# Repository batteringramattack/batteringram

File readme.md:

# Battering RAM: Low-Cost Interposer Attacks on Confidential Computing via Dynamic Memory Aliasing

This repository contains the hardware design and firmware for the interposer, tools, and proof-of-concept and end-to-end attacks presented in our paper.

## Directory structure

This repository is organized as follows.

* `./ddr4-interposer` contains the hardware design for the DDR4 interposer.
* `./interposer-control` contains the firmware for the DDR4 interposer.
* `./scalable-sgx-attacks` contains contains the PoC and E2E attacks on Scalable SGX.

## Getting started

### Hardware requirements

This artifact requires a custom DDR4 interposer to introduce dynamic memory aliases. The hardware schematic and PCB files for this interposer can be found in `./ddr4-interposer`. Below is the bill of materials.

| **Component**     | **Cost**  | **Qty.** | **Part number**        |
|-------------------|-------|:----:|---------------------|
| DIMM Connector    | $16   | 1    | CONN-DDR4-288-SM    |
| Raspberry Pi Pico | $5    | 1    | Raspberry Pi Pico 2 |
| Analog Switches   | $4    | 2    | ADG902BRMZ          |
| Voltage regulator | $0.65 | 1    | LD1117S25TR         |
| Resistor, 0402, 1kOhm     | $0.005 | 2    |            |
| Capacitor, 0603, 100nF    | $0.02  | 3    |            |
| Capacitor, 1206, 10uF     | $0.018 | 1    |            |

### Creating aliases

The interposer creates aliases by tying certain row address lines to ground. This causes aliases in the CPU's physical memory space as the DIMM now always sees a low signal, regardless of the address sent out by the CPU.

The interposer has five footprints that can be populated with switches. These footprints are labeled in the silkscreen. These include three footprints for inserting the switches on the A11, A13, and A17 lines (labeled "A11->A11", "A13->A13", and "A17->A17", respectively).
If a switch is not installed in a footprint, a jumper must be soldered in its place to connect the CPU and DIMM lines without interruption.

Additionally, to bypass RCD parity checking, two additional footprints optionally allow the A11 or A13 signals to be redirected to A17 (labeled "A11->A17" and "A13->A17", respectively).
Note that only one of these footprints can be occupied at a time. These switches can also not be used in conjunction with the "A17->A17" switch. When installing a switch on these footprints, you must also connect the corresponding jumper to connect it to the A17 line on the DIMM side.

### Mapping out unstable and aliased regions in Linux

When RCD parity is enabled, unstable memory regions are created where only a single bit is flipped, resulting in a parity error. Additionally, writes to aliased memory regions while the interposer is active may accidentally overwrite critical memory regions, potentially causing the system to crash.
To avoid these issues, the use of both the unstable regions and aliased regions can be prevented by using the `memmap` kernel parameter:
```
memmap=nn$ss
```
This will mark region `ss` to `ss+nn` as reserved. Note that using this parameter in GRUB requires escaping the `$` as `\$`. If you enter it through `/etc/default/grub`, you also have to escape the `\`:
```
GRUB_CMDLINE_LINUX_DEFAULT="memmap=nn\\\$ss"
```

## Cite

```
@inproceedings{batteringramsp26,
  title     = {{Battering RAM}: Low-Cost Interposer Attacks on Confidential Computing via Dynamic Memory Aliasings},
  author    = {De Meulemeester, Jesse and Oswald, David and Verbauwhede, Ingrid and Van Bulck, Jo},
  booktitle = {47th {IEEE} Symposium on Security and Privacy ({S\&P})},
  month     = May,
  year      = 2026,
}
```

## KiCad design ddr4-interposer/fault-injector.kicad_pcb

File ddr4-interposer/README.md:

# Battering RAM interposer

This directory contains the schematics and PCB layout (KiCad) of the Battering RAM interposer.

The interposer is configurable: it has several footprints for analog switches, of which only a few are populated, depending on which address lines you want to manipulate. The sections below describe which parts are always required, which depend on the configuration, and the configurations we used in the paper.

## Bill of materials

| Description               | Reference             | Part number         | Populate          |
|---------------------------|-----------------------|---------------------|-------------------|
| DDR4 DIMM connector       | J2                    | CONN-DDR4-288-SM    | Always            |
| Raspberry Pi Pico 2       | U3                    | Raspberry Pi Pico 2 | Always            |
| Voltage regulator, 2.5 V  | U8                    | LD1117S25TR         | Always            |
| Capacitor, 1206, 10 µF    | C9                    |                     | Always            |
| Capacitor, 0603, 100 nF   | C8                    |                     | Always            |
| Analog switch             | U1, U2, U4–U7, U9     | ADG902BRMZ          | Per configuration |
| Resistor, 0402, 1 kΩ      | R1–R7                 |                     | Per configuration |
| Capacitor, 0603, 100 nF   | C1–C7                 |                     | Per configuration |
| Jumper, 0402, 0 Ω         | R8, R9, R11, R13, R17 |                     | Per configuration |

## Switch positions

The interposer has seven switch positions:

- **In-line switches** (U4, U1, U6) sit in the path of the A11, A13 and A17 command/address (CA) lines. They are labeled `Axx -> Axx` on the silkscreen.
- **Redirect switches** (U5, U2) connect the CPU-side A11 or A13 line to the DIMM-side A17 line. They are labeled `Axx -> A17` on the silkscreen. To connect the switch output to the DIMM, the output jumper must be populated.
- **General-purpose switches** (U7, U9) are not connected to any signal. They can be wired to any signal by cutting the bridged jumpers and connecting them to the test points using using thin enameled (magnet) wire.

Each switch has its own pull-up resistor and decoupling capacitor. Each in-line switch also has a passthrough jumper that connects the line directly when the switch is not populated.

| Switch  | CPU-side line | DIMM-side line | Passthrough jumper | Pull-up | Decoupling cap | Output Jumper |
|:-------:|:-------------:|:--------------:|:------------------:|:-------:|:--------------:|:-------------:|
| U4      | A11           | A11            | R11                | R4      | C2             | -             |
| U1      | A13           | A13            | R13                | R1      | C3             | -             |
| U6      | A17           | A17            | R17                | R5      | C5             | -             |
| U5      | A11           | A17            | –                  | R3      | C4             | R8            |
| U2      | A13           | A17            | –                  | R2      | C1             | R9            |
| U7      | TP2 / TP11    | TP6 / TP12     | –                  | R6      | C6             | -             |
| U9      | TP8 / TP9     | TP7 / TP10     | –                  | R7      | C7             | -             |

## Configuring the interposer
 
Each populated switch needs a pull-up resistor (1 kΩ) and a 100 nF decoupling capacitor, see the table above. In-line switches (U4, U1, U6) that are left unpopulated need their passthrough jumper instead, otherwise the corresponding address line is not connected to the DIMM. The exception is A17 when one of the redirect switches (U5, U2) is installed: the redirect switch then drives A17, so R17 is left unpopulated.
 
> [!NOTE]
> Each DIMM-side line must be driven by exactly one path: its in-line switch, its passthrough jumper, or (for A17) one of the redirect switches. For example, populating both U5 (A11 -> A17) and U6 (A17 -> A17), or U2 (A13 -> A17) together with R17, is invalid, as both would drive A17 on the DIMM.

### Bridged jumpers on other signals

Besides the switch positions, many other signals pass through 0402 jumper footprints (JP1–JP20 and JP23–JP43) that are bridged on the PCB by default. This includes most of the CA bus (all address lines except A11, A13 and A17, which go through the switch positions), the clock, reset and chip-select lines, among others. These signals work as-is without populating anything.

To manipulate one of these signals, cut the bridge between the jumper pads to interrupt the line, and wire the two pads to one of the general-purpose switches (U7, U9). To restore the original connection later, simply solder a 0402 0 Ω resistor onto the footprint.

## Configurations used in the paper

### Single switch (Figure 5a)

| Populate                               | Passthrough jumpers |
|----------------------------------------|---------------------|
| U1 (A13 -> A13) with R1, C3            | R11, R17            |

### Redirecting an address line (Figure 5b)

| Populate                               | Passthrough jumpers |
|----------------------------------------|---------------------|
| U1 (A13 -> A13) with R1, C3            | R11                 |
| U2 (A13 -> A17) with R2, C1, R9        |                     |

### Dual switches (Figure 5c)

| Populate                               | Passthrough jumpers |
|----------------------------------------|---------------------|
| U4 (A11 -> A11) with R4, C2            | R17                 |
| U1 (A13 -> A13) with R1, C3            |                     |

## Fabrication

Recommended settings when ordering the PCB:

- Layers: 4
- PCB thickness: 1.6 mm (or 1.4 mm if available, see note below)
- Min via: 0.2 mm drill / 0.35 mm diameter
- Surface finish: ENIG
- Copper weight: 1 oz outer / 0.5 oz inner
- Everything else: fab default settings (no controlled impedance or special stack-up required)

> [!NOTE]
> 1.6 mm is slightly thicker than regular DDR4 memory modules (1.4 mm). To avoid damaging the motherboard's DIMM socket, it is recommended to use a DDR4 DIMM extender between the motherboard and the interposer.

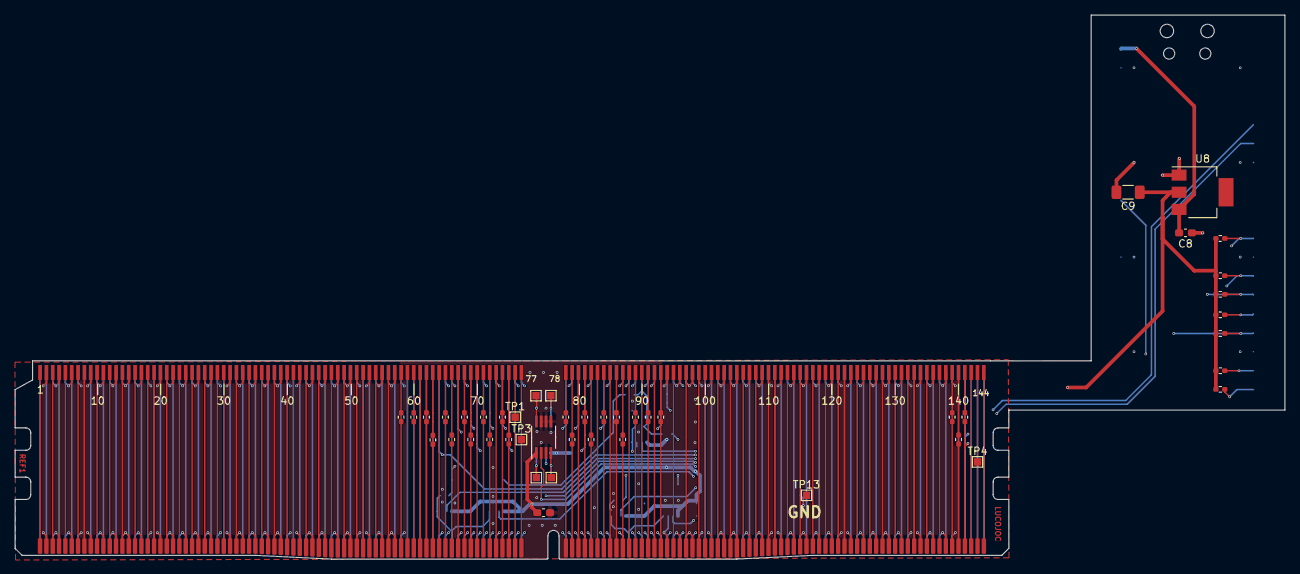
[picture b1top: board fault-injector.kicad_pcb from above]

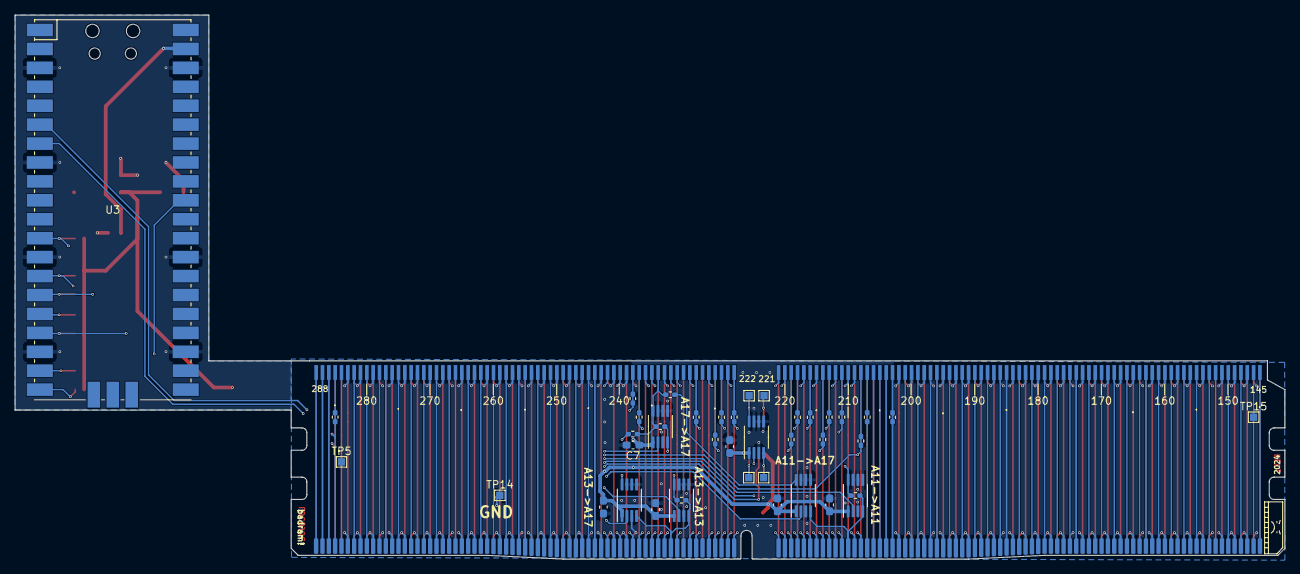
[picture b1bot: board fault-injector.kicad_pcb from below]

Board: 4 copper layers, 170.4 x 73.0 mm, 88 parts (41 on the bottom side), 219 nets.

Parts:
C1, C2, C3, C4, C5, C6, C7: C_Small; C_0603_1608Metric_Pad1.08x0.95mm_HandSolder
C8: 100nF; C_0603_1608Metric_Pad1.08x0.95mm_HandSolder
C9: 10uF; C_1206_3216Metric_Pad1.33x1.80mm_HandSolder
J1: DDR4_to_MB; ddr4-edge-conn-male
J2: DDR4_to_DIMM; ddr4-edge-conn-female-badram
JP1, JP2, JP3, JP4, JP5, JP6, JP7, JP8, JP9, JP10, JP11, JP12, JP13, JP14, JP15, JP16, JP17, JP18, JP19, JP20, JP23, JP24, JP25, JP26, JP27, JP28, JP29, JP30, JP31, JP32, JP33, JP34, JP35, JP36, JP37, JP38, JP39, JP40, JP41, JP42, JP43: Jumper_2_Bridged; Jumper_0402_bridged
R1, R2, R3, R4, R5, R6, R7: 1k; R_0402_1005Metric_Pad0.72x0.64mm_HandSolder
R8, R9: 0; R_0402_1005Metric_Pad0.72x0.64mm_HandSolder
R11, R13, R17: 0R; R_0402_1005Metric_Pad0.72x0.64mm_HandSolder
TP1, TP2, TP3, TP4, TP5, TP6, TP7, TP8, TP9, TP10, TP11, TP12, TP13, TP14, TP15: TestPoint; TestPoint_Pad_1.0x1.0mm
U1, U2, U4, U5, U6, U7, U9: ADG902BRMZ; MSOP-8_3x3mm_P0.65mm
U3: Pico; RPi_Pico_SMD_TH
U8: LD1117S25TR_SOT223; SOT-223-3_TabPin2

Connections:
A0_DIMM: J2.79 (A0), JP43.2 (B)
A0_MB: J1.79 (A0), JP43.1 (A)
A1_DIMM: J2.72 (A1), JP42.2 (B)
A1_MB: J1.72 (A1), JP42.1 (A)
A2_DIMM: J2.216 (A2), JP41.2 (B)
A2_MB: J1.216 (A2), JP41.1 (A)
A3_DIMM: J2.71 (A3), JP40.2 (B)
A3_MB: J1.71 (A3), JP40.1 (A)
A4_DIMM: J2.214 (A4), JP39.2 (B)
A4_MB: J1.214 (A4), JP39.1 (A)
A5_DIMM: J2.213 (A5), JP38.2 (B)
A5_MB: J1.213 (A5), JP38.1 (A)
A6_DIMM: J2.69 (A6), JP37.2 (B)
A6_MB: J1.69 (A6), JP37.1 (A)
A7_DIMM: J2.211 (A7), JP36.2 (B)
A7_MB: J1.211 (A7), JP36.1 (A)
A8_DIMM: J2.68 (A8), JP35.2 (B)
A8_MB: J1.68 (A8), JP35.1 (A)
A9_DIMM: J2.66 (A9), JP34.2 (B)
A9_MB: J1.66 (A9), JP34.1 (A)
A10_AP_DIMM: J2.225 (A10/AP), JP33.2 (B)
A10_AP_MB: J1.225 (A10/AP), JP33.1 (A)
A11_DIMM: J2.210 (A11), R11.2, U4.8 (RF2)
A11_MB: J1.210 (A11), R11.1, U4.4 (RF1), U5.4 (RF1)
A12_BC_n_DIMM: J2.65 (A12/BC_n), JP32.2 (B)
A12_BC_n_MB: J1.65 (A12/BC_n), JP32.1 (A)
A13_DIMM: J2.232 (A13), R13.2, U1.8 (RF2)
A13_MB: J1.232 (A13), R13.1, U1.4 (RF1), U2.4 (RF1)
A17_DIMM: J2.234 (A17), R8.1, R9.1, R17.2, U6.8 (RF2)
A17_MB: J1.234 (A17), R17.1, U6.4 (RF1)
ACT_n_DIMM: J2.62 (ACT_n), JP12.2 (B)
ACT_n_MB: J1.62 (ACT_n), JP12.1 (A)
ALERT_n_DIMM: J2.208 (ALERT_n), JP20.2 (B)
ALERT_n_MB: J1.208 (ALERT_n), JP20.1 (A), U3.31 (GPIO26_ADC0)
BA0_DIMM: J2.81 (BA0), JP28.2 (B)
BA0_MB: J1.81 (BA0), JP28.1 (A)
BA1_DIMM: J2.224 (BA1), JP27.2 (B)
BA1_MB: J1.224 (BA1), JP27.1 (A)
BG0_DIMM: J2.63 (BG0), JP9.2 (B)
BG0_MB: J1.63 (BG0), JP9.1 (A)
BG1_DIMM: J2.207 (BG1), JP8.2 (B)
BG1_MB: J1.207 (BG1), JP8.1 (A)
CAS_n_A15_DIMM: J2.86 (CAS_n/A15), JP30.2 (B)
CAS_n_A15_MB: J1.86 (CAS_n/A15), JP30.1 (A)
CB0_DIMM: J1.49 (CB0), J2.49 (CB0)
CB1_DIMM: J1.194 (CB1), J2.194 (CB1)
CB2_DIMM: J1.56 (CB2), J2.56 (CB2)
CB3_DIMM: J1.201 (CB3), J2.201 (CB3)
CB4_DIMM: J1.47 (CB4), J2.47 (CB4)
CB5_DIMM: J1.192 (CB5), J2.192 (CB5)
CB6_DIMM: J1.54 (CB6), J2.54 (CB6)
CB7_DIMM: J1.199 (CB7), J2.199 (CB7)
CK0_c_DIMM: J2.75 (CK0_c), JP6.2 (B)
CK0_c_MB: J1.75 (CK0_c), JP6.1 (A)
CK0_t_DIMM: J2.74 (CK0_t), JP5.2 (B)
CK0_t_MB: J1.74 (CK0_t), JP5.1 (A)
CK1_c_DIMM: J2.219 (CK1_c), JP3.2 (B)
CK1_c_MB: J1.219 (CK1_c), JP3.1 (A)
CK1_t_DIMM: J2.218 (CK1_t), JP2.2 (B)
CK1_t_MB: J1.218 (CK1_t), JP2.1 (A)
CKE0_DIMM: J2.60 (CKE0), JP7.2 (B)
CKE0_MB: J1.60 (CKE0), JP7.1 (A)
CKE1_NC_DIMM: J2.203 (CKE1/NC), JP4.2 (B)
CKE1_NC_MB: J1.203 (CKE1/NC), JP4.1 (A)
CS0_n_DIMM: J2.84 (CS0_n), JP26.2 (B)
CS0_n_MB: J1.84 (CS0_n), JP26.1 (A)
CS1_n_NC_DIMM: J2.89 (CS1_n/NC), JP25.2 (B)
CS1_n_NC_MB: J1.89 (CS1_n/NC), JP25.1 (A)
CS2_n_C0_DIMM: J2.93 (CS2_n/C0), JP24.2 (B)
CS2_n_C0_MB: J1.93 (CS2_n/C0), JP24.1 (A)
CS3_n_C1,NC_DIMM: J2.237 (CS3_n/C1,NC), JP23.2 (B)
CS3_n_C1,NC_MB: J1.237 (CS3_n/C1,NC), JP23.1 (A)
DQ0_DIMM: J1.5 (DQ0), J2.5 (DQ0)
DQ1_DIMM: J1.150 (DQ1), J2.150 (DQ1)
DQ2_DIMM: J1.12 (DQ2), J2.12 (DQ2)
DQ3_DIMM: J1.157 (DQ3), J2.157 (DQ3)
DQ4_DIMM: J1.3 (DQ4), J2.3 (DQ4)
DQ5_DIMM: J1.148 (DQ5), J2.148 (DQ5)
DQ6_DIMM: J1.10 (DQ6), J2.10 (DQ6)
DQ7_DIMM: J1.155 (DQ7), J2.155 (DQ7)
DQ8_DIMM: J1.16 (DQ8), J2.16 (DQ8)
DQ9_DIMM: J1.161 (DQ9), J2.161 (DQ9)
DQ10_DIMM: J1.23 (DQ10), J2.23 (DQ10)
DQ11_DIMM: J1.168 (DQ11), J2.168 (DQ11)
DQ12_DIMM: J1.14 (DQ12), J2.14 (DQ12)
DQ13_DIMM: J1.159 (DQ13), J2.159 (DQ13)
DQ14_DIMM: J1.21 (DQ14), J2.21 (DQ14)
DQ15_DIMM: J1.166 (DQ15), J2.166 (DQ15)
DQ16_DIMM: J1.27 (DQ16), J2.27 (DQ16)
DQ17_DIMM: J1.172 (DQ17), J2.172 (DQ17)
DQ18_DIMM: J1.34 (DQ18), J2.34 (DQ18)
DQ19_DIMM: J1.179 (DQ19), J2.179 (DQ19)
DQ20_DIMM: J1.25 (DQ20), J2.25 (DQ20)
DQ21_DIMM: J1.170 (DQ21), J2.170 (DQ21)
DQ22_DIMM: J1.32 (DQ22), J2.32 (DQ22)
DQ23_DIMM: J1.177 (DQ23), J2.177 (DQ23)
DQ24_DIMM: J1.38 (DQ24), J2.38 (DQ24)
DQ25_DIMM: J1.183 (DQ25), J2.183 (DQ25)
DQ26_DIMM: J1.45 (DQ26), J2.45 (DQ26)
DQ27_DIMM: J1.190 (DQ27), J2.190 (DQ27)
DQ28_DIMM: J1.36 (DQ28), J2.36 (DQ28)
DQ29_DIMM: J1.181 (DQ29), J2.181 (DQ29)
DQ30_DIMM: J1.43 (DQ30), J2.43 (DQ30)
DQ31_DIMM: J1.188 (DQ31), J2.188 (DQ31)
DQ32_DIMM: J1.97 (DQ32), J2.97 (DQ32)
DQ33_DIMM: J1.242 (DQ33), J2.242 (DQ33)
DQ34_DIMM: J1.104 (DQ34), J2.104 (DQ34)
DQ35_DIMM: J1.249 (DQ35), J2.249 (DQ35)
DQ36_DIMM: J1.95 (DQ36), J2.95 (DQ36)
DQ37_DIMM: J1.240 (DQ37), J2.240 (DQ37)
DQ38_DIMM: J1.102 (DQ38), J2.102 (DQ38)
DQ39_DIMM: J1.247 (DQ39), J2.247 (DQ39)
DQ40_DIMM: J1.108 (DQ40), J2.108 (DQ40)
DQ41_DIMM: J1.253 (DQ41), J2.253 (DQ41)
DQ42_DIMM: J1.115 (DQ42), J2.115 (DQ42)
DQ43_DIMM: J1.260 (DQ43), J2.260 (DQ43)
DQ44_DIMM: J1.106 (DQ44), J2.106 (DQ44)
DQ45_DIMM: J1.251 (DQ45), J2.251 (DQ45)
DQ46_DIMM: J1.113 (DQ46), J2.113 (DQ46)
DQ47_DIMM: J1.258 (DQ47), J2.258 (DQ47)
DQ48_DIMM: J1.119 (DQ48), J2.119 (DQ48)
DQ49_DIMM: J1.264 (DQ49), J2.264 (DQ49)
DQ50_DIMM: J1.126 (DQ50), J2.126 (DQ50)
DQ51_DIMM: J1.271 (DQ51), J2.271 (DQ51)
DQ52_DIMM: J1.117 (DQ52), J2.117 (DQ52)
DQ53_DIMM: J1.262 (DQ53), J2.262 (DQ53)
DQ54_DIMM: J1.124 (DQ54), J2.124 (DQ54)
DQ55_DIMM: J1.269 (DQ55), J2.269 (DQ55)
DQ56_DIMM: J1.130 (DQ56), J2.130 (DQ56)
DQ57_DIMM: J1.275 (DQ57), J2.275 (DQ57)
DQ58_DIMM: J1.137 (DQ58), J2.137 (DQ58)
DQ59_DIMM: J1.282 (DQ59), J2.282 (DQ59)
DQ60_DIMM: J1.128 (DQ60), J2.128 (DQ60)
DQ61_DIMM: J1.273 (DQ61), J2.273 (DQ61)
DQ62_DIMM: J1.135 (DQ62), J2.135 (DQ62)
DQ63_DIMM: J1.280 (DQ63), J2.280 (DQ63)
DQS0_c_DIMM: J1.152 (DQS0_c), J2.152 (DQS0_c)
DQS0_t_DIMM: J1.153 (DQS0_t), J2.153 (DQS0_t)
DQS1_c_DIMM: J1.163 (DQS1_c), J2.163 (DQS1_c)
DQS1_t_DIMM: J1.164 (DQS1_t), J2.164 (DQS1_t)
DQS2_c_DIMM: J1.174 (DQS2_c), J2.174 (DQS2_c)
DQS2_t_DIMM: J1.175 (DQS2_t), J2.175 (DQS2_t)
DQS3_c_DIMM: J1.185 (DQS3_c), J2.185 (DQS3_c)
DQS3_t_DIMM: J1.186 (DQS3_t), J2.186 (DQS3_t)
DQS4_c_DIMM: J1.244 (DQS4_c), J2.244 (DQS4_c)
DQS4_t_DIMM: J1.245 (DQS4_t), J2.245 (DQS4_t)
DQS5_c_DIMM: J1.255 (DQS5_c), J2.255 (DQS5_c)
DQS5_t_DIMM: J1.256 (DQS5_t), J2.256 (DQS5_t)
DQS6_c_DIMM: J1.266 (DQS6_c), J2.266 (DQS6_c)
DQS6_t_DIMM: J1.267 (DQS6_t), J2.267 (DQS6_t)
DQS7_c_DIMM: J1.277 (DQS7_c), J2.277 (DQS7_c)
DQS7_t_DIMM: J1.278 (DQS7_t), J2.278 (DQS7_t)
DQS8_c_DIMM: J1.196 (DQS8_c), J2.196 (DQS8_c)
DQS8_t_DIMM: J1.197 (DQS8_t), J2.197 (DQS8_t)
DQS09_c_TDQS9_c_DIMM: J1.8 (DQS09_c/TDQS9_c), J2.8 (DQS09_c/TDQS9_c)
DQS9_t_TDQS9_t_DIMM: J1.7 (DQS9_t/TDQS9_t), J2.7 (DQS9_t/TDQS9_t)
DQS10_c_TDQS10_c_DIMM: J1.19 (DQS10_c/TDQS10_c), J2.19 (DQS10_c/TDQS10_c)
DQS10_t_TDQS10_t_DIMM: J1.18 (DQS10_t/TDQS10_t), J2.18 (DQS10_t/TDQS10_t)
DQS11_c_TDQS11_c_DIMM: J1.30 (DQS11_c/TDQS11_c), J2.30 (DQS11_c/TDQS11_c)
DQS11_t_TDQS11_t_DIMM: J1.29 (DQS11_t/TDQS11_t), J2.29 (DQS11_t/TDQS11_t)
DQS12_c_TDQS12_c_DIMM: J1.41 (DQS12_c/TDQS12_c), J2.41 (DQS12_c/TDQS12_c)
DQS12_t_TDQS12_t_DIMM: J1.40 (DQS12_t/TDQS12_t), J2.40 (DQS12_t/TDQS12_t)
DQS13_c_TDQS13_c_DIMM: J1.100 (DQS13_c/TDQS13_c), J2.100 (DQS13_c/TDQS13_c)
DQS13_t_TDQ13_t_DIMM: J1.99 (DQS13_t/TDQ13_t), J2.99 (DQS13_t/TDQ13_t)
DQS14_c_TDQS14_c_DIMM: J1.111 (DQS14_c/TDQS14_c), J2.111 (DQS14_c/TDQS14_c)
DQS14_t_TDQS14_t_DIMM: J1.110 (DQS14_t/TDQS14_t), J2.110 (DQS14_t/TDQS14_t)
DQS15_c_TDQS15_c_DIMM: J1.122 (DQS15_c/TDQS15_c), J2.122 (DQS15_c/TDQS15_c)
DQS15_t_TDQS15_t_DIMM: J1.121 (DQS15_t/TDQS15_t), J2.121 (DQS15_t/TDQS15_t)
DQS16_c_TDQS16_c_DIMM: J1.133 (DQS16_c/TDQS16_c), J2.133 (DQS16_c/TDQS16_c)
DQS16_t_TDQS16_t_DIMM: J1.132 (DQS16_t/TDQS16_t), J2.132 (DQS16_t/TDQS16_t)
DQS17_c_TDQS17_c_DIMM: J1.52 (DQS17_c/TDQS17_c), J2.52 (DQS17_c/TDQS17_c)
DQS17_t_TDQS17_t_DIMM: J1.51 (DQS17_t/TDQS17_t), J2.51 (DQS17_t/TDQS17_t)
EVENT_n_DIMM: J2.78 (EVENT_n), JP14.2 (B)
EVENT_n_MB: J1.78 (EVENT_n), JP14.1 (A)
GP9: R7.2, U3.12 (GPIO9), U9.2 (CTRL)
GP10: R6.2, U3.14 (GPIO10), U7.2 (CTRL)
GP11: R5.2, U3.15 (GPIO11), U6.2 (CTRL)
GP12: R3.2, U3.16 (GPIO12), U5.2 (CTRL)
GP13: R4.2, U3.17 (GPIO13), U4.2 (CTRL)
GP14: R2.2, U2.2 (CTRL), U3.19 (GPIO14)
GP15: R1.2, U1.2 (CTRL), U3.20 (GPIO15)
NC_C2_DIMM: J1.235 (NC/C2), J2.235 (NC/C2)
NC_DIMM: J1.1 (NC), J1.144 (NC), J1.145 (NC), J1.205 (NC), J1.227 (NC), J1.230 (NC), J2.1 (NC), J2.144 (NC), J2.145 (NC), J2.205 (NC), J2.227 (NC), J2.230 (NC)
unnamed: R9.2, U2.8 (RF2)
unnamed: C8.1, U3.39 (VSYS), U8.3 (VI)
unnamed: R8.2, U5.8 (RF2)
unnamed: TP2.1, TP11.1, U7.4 (RF1)
unnamed: TP6.1, TP12.1, U7.8 (RF2)
unnamed: TP8.1, TP9.1, U9.4 (RF1)
unnamed: TP7.1, TP10.1, U9.8 (RF2)
ODT0_DIMM: J2.87 (ODT0), JP10.2 (B)
ODT0_MB: J1.87 (ODT0), JP10.1 (A)
ODT1_NC_DIMM: J2.91 (ODT1/NC), JP11.2 (B)
ODT1_NC_MB: J1.91 (ODT1/NC), JP11.1 (A)
PARITY_DIMM: J2.222 (PARITY), JP13.2 (B)
PARITY_MB: J1.222 (PARITY), JP13.1 (A)
RAS_n_A16_DIMM: J2.82 (RAS_n/A16), JP29.2 (B)
RAS_n_A16_MB: J1.82 (RAS_n/A16), JP29.1 (A)
RESET_n_DIMM: J2.58 (RESET_n), JP1.2 (B)
RESET_n_MB: J1.58 (RESET_n), JP1.1 (A)
SA0_DIMM: J2.139 (SA0), JP17.2 (B)
SA0_MB: J1.139 (SA0), JP17.1 (A)
SA1_DIMM: J2.140 (SA1), JP18.2 (B)
SA1_MB: J1.140 (SA1), JP18.1 (A)
SA2_DIMM: J2.238 (SA2), JP19.2 (B)
SA2_MB: J1.238 (SA2), JP19.1 (A)
SCL_DIMM: J2.141 (SCL), JP15.2 (B)
SCL_MB: J1.141 (SCL), JP15.1 (A), U3.7 (GPIO5)
SDA_DIMM: J2.285 (SDA), JP16.2 (B)
SDA_MB: J1.285 (SDA), JP16.1 (A), U3.6 (GPIO4)
VDDSPD_DIMM: J1.284 (VDDSPD), J2.284 (VDDSPD), TP5.1
VDD_DIMM: J1.59 (VDD), J1.61 (VDD), J1.64 (VDD), J1.67 (VDD), J1.70 (VDD), J1.73 (VDD), J1.76 (VDD), J1.80 (VDD), J1.83 (VDD), J1.85 (VDD), J1.88 (VDD), J1.90 (VDD), J1.92 (VDD), J1.204 (VDD), J1.206 (VDD), J1.209 (VDD), J1.212 (VDD), J1.215 (VDD), J1.217 (VDD), J1.220 (VDD), J1.223 (VDD), J1.226 (VDD), J1.229 (VDD), J1.231 (VDD), J1.233 (VDD), J1.236 (VDD), J2.59 (VDD), J2.61 (VDD), J2.64 (VDD), J2.67 (VDD), J2.70 (VDD), J2.73 (VDD), J2.76 (VDD), J2.80 (VDD), J2.83 (VDD), J2.85 (VDD), J2.88 (VDD), J2.90 (VDD), J2.92 (VDD), J2.204 (VDD), J2.206 (VDD), J2.209 (VDD), J2.212 (VDD), J2.215 (VDD), J2.217 (VDD), J2.220 (VDD), J2.223 (VDD), J2.226 (VDD), J2.229 (VDD), J2.231 (VDD), J2.233 (VDD), J2.236 (VDD), TP1.1
VDD_SW: C1.1, C2.1, C3.1, C4.1, C5.1, C6.1, C7.1, C9.1, R1.1, R2.1, R3.1, R4.1, R5.1, R6.1, R7.1, U1.1 (VDD), U2.1 (VDD), U4.1 (VDD), U5.1 (VDD), U6.1 (VDD), U7.1 (VDD), U8.2 (VO), U9.1 (VDD)
VPP_DIMM: J1.142 (VPP), J1.143 (VPP), J1.286 (VPP), J1.287 (VPP), J1.288 (VPP), J2.142 (VPP), J2.143 (VPP), J2.286 (VPP), J2.287 (VPP), J2.288 (VPP), TP4.1
VREFCA_DIMM: J1.146 (VREFCA), J2.146 (VREFCA), TP15.1
VSS_DIMM: C1.2, C2.2, C3.2, C4.2, C5.2, C6.2, C7.2, C8.2, C9.2, J1.2 (VSS), J1.4 (VSS), J1.6 (VSS), J1.9 (VSS), J1.11 (VSS), J1.13 (VSS), J1.15 (VSS), J1.17 (VSS), J1.20 (VSS), J1.22 (VSS), J1.24 (VSS), J1.26 (VSS), J1.28 (VSS), J1.31 (VSS), J1.33 (VSS), J1.35 (VSS), J1.37 (VSS), J1.39 (VSS), J1.42 (VSS), J1.44 (VSS), J1.46 (VSS), J1.48 (VSS), J1.50 (VSS), J1.53 (VSS), J1.55 (VSS), J1.57 (VSS), J1.94 (VSS), J1.96 (VSS), J1.98 (VSS), J1.101 (VSS), J1.103 (VSS), J1.105 (VSS), J1.107 (VSS), J1.109 (VSS), J1.112 (VSS), J1.114 (VSS), J1.116 (VSS), J1.118 (VSS), J1.120 (VSS), J1.123 (VSS), J1.125 (VSS), J1.127 (VSS), J1.129 (VSS), J1.131 (VSS), J1.134 (VSS), J1.136 (VSS), J1.138 (VSS), J1.147 (VSS), J1.149 (VSS), J1.151 (VSS), J1.154 (VSS), J1.156 (VSS), J1.158 (VSS), J1.160 (VSS), J1.162 (VSS), J1.165 (VSS), J1.167 (VSS), J1.169 (VSS), J1.171 (VSS), J1.173 (VSS), J1.176 (VSS), J1.178 (VSS), J1.180 (VSS), J1.182 (VSS), J1.184 (VSS), J1.187 (VSS), J1.189 (VSS), J1.191 (VSS), J1.193 (VSS), J1.195 (VSS), J1.198 (VSS), J1.200 (VSS), J1.202 (VSS), J1.239 (VSS), J1.241 (VSS), J1.243 (VSS), J1.246 (VSS), J1.248 (VSS), J1.250 (VSS), J1.252 (VSS), J1.254 (VSS), J1.257 (VSS), J1.259 (VSS), J1.261 (VSS), J1.263 (VSS), J1.265 (VSS), J1.268 (VSS), J1.270 (VSS), J1.272 (VSS), J1.274 (VSS), J1.276 (VSS), J1.279 (VSS), J1.281 (VSS), J1.283 (VSS), J2.2 (VSS), J2.4 (VSS), J2.6 (VSS), J2.9 (VSS), J2.11 (VSS), J2.13 (VSS), J2.15 (VSS), J2.17 (VSS), J2.20 (VSS), J2.22 (VSS), J2.24 (VSS), J2.26 (VSS), J2.28 (VSS), J2.31 (VSS), J2.33 (VSS), J2.35 (VSS), J2.37 (VSS), J2.39 (VSS), J2.42 (VSS), J2.44 (VSS), J2.46 (VSS), J2.48 (VSS), J2.50 (VSS), J2.53 (VSS), J2.55 (VSS), J2.57 (VSS), J2.94 (VSS), J2.96 (VSS), J2.98 (VSS), J2.101 (VSS), J2.103 (VSS), J2.105 (VSS), J2.107 (VSS), J2.109 (VSS), J2.112 (VSS), J2.114 (VSS), J2.116 (VSS), J2.118 (VSS), J2.120 (VSS), J2.123 (VSS), J2.125 (VSS), J2.127 (VSS), J2.129 (VSS), J2.131 (VSS), J2.134 (VSS), J2.136 (VSS), J2.138 (VSS), J2.147 (VSS), J2.149 (VSS), J2.151 (VSS), J2.154 (VSS), J2.156 (VSS), J2.158 (VSS), J2.160 (VSS), J2.162 (VSS), J2.165 (VSS), J2.167 (VSS), J2.169 (VSS), J2.171 (VSS), J2.173 (VSS), J2.176 (VSS), J2.178 (VSS), J2.180 (VSS), J2.182 (VSS), J2.184 (VSS), J2.187 (VSS), J2.189 (VSS), J2.191 (VSS), J2.193 (VSS), J2.195 (VSS), J2.198 (VSS), J2.200 (VSS), J2.202 (VSS), J2.239 (VSS), J2.241 (VSS), J2.243 (VSS), J2.246 (VSS), J2.248 (VSS), J2.250 (VSS), J2.252 (VSS), J2.254 (VSS), J2.257 (VSS), J2.259 (VSS), J2.261 (VSS), J2.263 (VSS), J2.265 (VSS), J2.268 (VSS), J2.270 (VSS), J2.272 (VSS), J2.274 (VSS), J2.276 (VSS), J2.279 (VSS), J2.281 (VSS), J2.283 (VSS), TP13.1, TP14.1, U1.3 (GND), U1.5 (GND), U1.6 (GND), U1.7 (GND), U2.3 (GND), U2.5 (GND), U2.6 (GND), U2.7 (GND), U3.3 (GND), U3.8 (GND), U3.13 (GND), U3.18 (GND), U3.23 (GND), U3.28 (GND), U3.38 (GND), U4.3 (GND), U4.5 (GND), U4.6 (GND), U4.7 (GND), U5.3 (GND), U5.5 (GND), U5.6 (GND), U5.7 (GND), U6.3 (GND), U6.5 (GND), U6.6 (GND), U6.7 (GND), U7.3 (GND), U7.5 (GND), U7.6 (GND), U7.7 (GND), U8.1 (GND), U9.3 (GND), U9.5 (GND), U9.6 (GND), U9.7 (GND)
VTT_DIMM: J1.77 (VTT), J1.221 (VTT), J2.77 (VTT), J2.221 (VTT), TP3.1
WE_n_A14_DIMM: J2.228 (WE_n/A14), JP31.2 (B)
WE_n_A14_MB: J1.228 (WE_n/A14), JP31.1 (A)

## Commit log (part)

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2025-10-01 readme.md: fix 'regardless' typo
2025-10-03 Minor typo fixes
2025-10-04 Update BOM
    Schematic and battering ram website show 100nF capacitor
